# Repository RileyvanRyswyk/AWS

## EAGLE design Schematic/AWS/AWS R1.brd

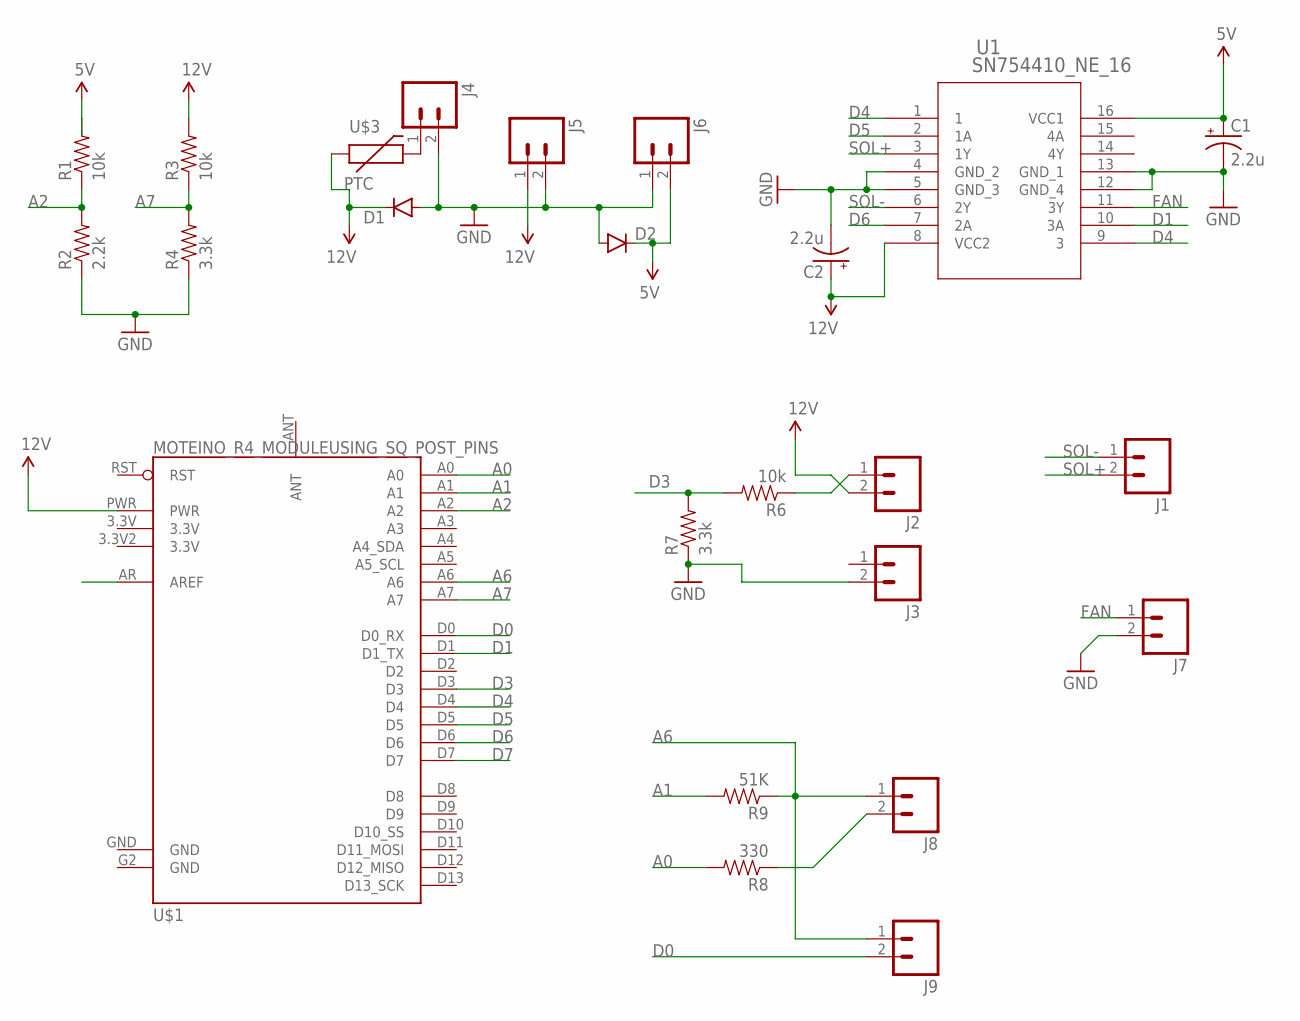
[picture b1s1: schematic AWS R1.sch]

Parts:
C1, C2: 2.2u; CPOL-RADIAL-100UF-25V
D1, D2: DIODEPTH; DIODE-1N4001
J1, J2, J3, J4, J5, J6, J7, J8, J9: M025MM; SCREWTERMINAL-5MM-2
R1, R3, R6: 10k; AXIAL-0.4
R2: 2.2k; AXIAL-0.4
R4, R7: 3.3k; AXIAL-0.4
R8: 330; AXIAL-0.4
R9: 51K; AXIAL-0.4
U1: SN754410_NE_16; NE16
U$1: MOTEINO_R4_MODULEUSING_SQ_POST_PINS; MOTEINTO_R4_SQ
U$3: PTC; MC331XX

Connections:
5V: C1.1 (+), D2.C, J6.2, R1.P$2 (2), U1.16 (VCC1)
12V: C2.1 (+), D1.C, J2.2, J5.1, R3.P$2 (2), U1.8 (VCC2), U$1.PWR, U$3.P$1 (1)
A0: R8.P$2 (2), U$1.A0
A1: R9.P$2 (2), U$1.A1
A2: R1.P$1 (1), R2.P$2 (2), U$1.A2
A6: J8.1, J9.1, R9.P$1 (1), U$1.A6
A7: R3.P$1 (1), R4.P$2 (2), U$1.A7
D0: J9.2, U$1.D0 (D0_RX)
D1: U1.10 (3A), U$1.D1 (D1_TX)
D3: R6.P$2 (2), R7.P$2 (2), U$1.D3
D4: U1.1, U1.9 (3), U$1.D4
D5: U1.2 (1A), U$1.D5
D6: U1.7 (2A), U$1.D6
D7: U$1.D7
FAN: J7.1, U1.11 (3Y)
GND: C1.2 (-), C2.2 (-), D1.A, D2.A, J3.2, J4.2, J5.2, J6.1, J7.2, R2.P$1 (1), R4.P$1 (1), R7.P$1 (1), U1.4 (GND_2), U1.5 (GND_3), U1.12 (GND_4), U1.13 (GND_1), U$1.G2 (GND), U$1.GND
unnamed: J8.2, R8.P$1 (1)
unnamed: J2.1, R6.P$1 (1)
unnamed: J4.1, U$3.P$2 (2)
SOL+: J1.2, U1.3 (1Y)
SOL-: J1.1, U1.6 (2Y)

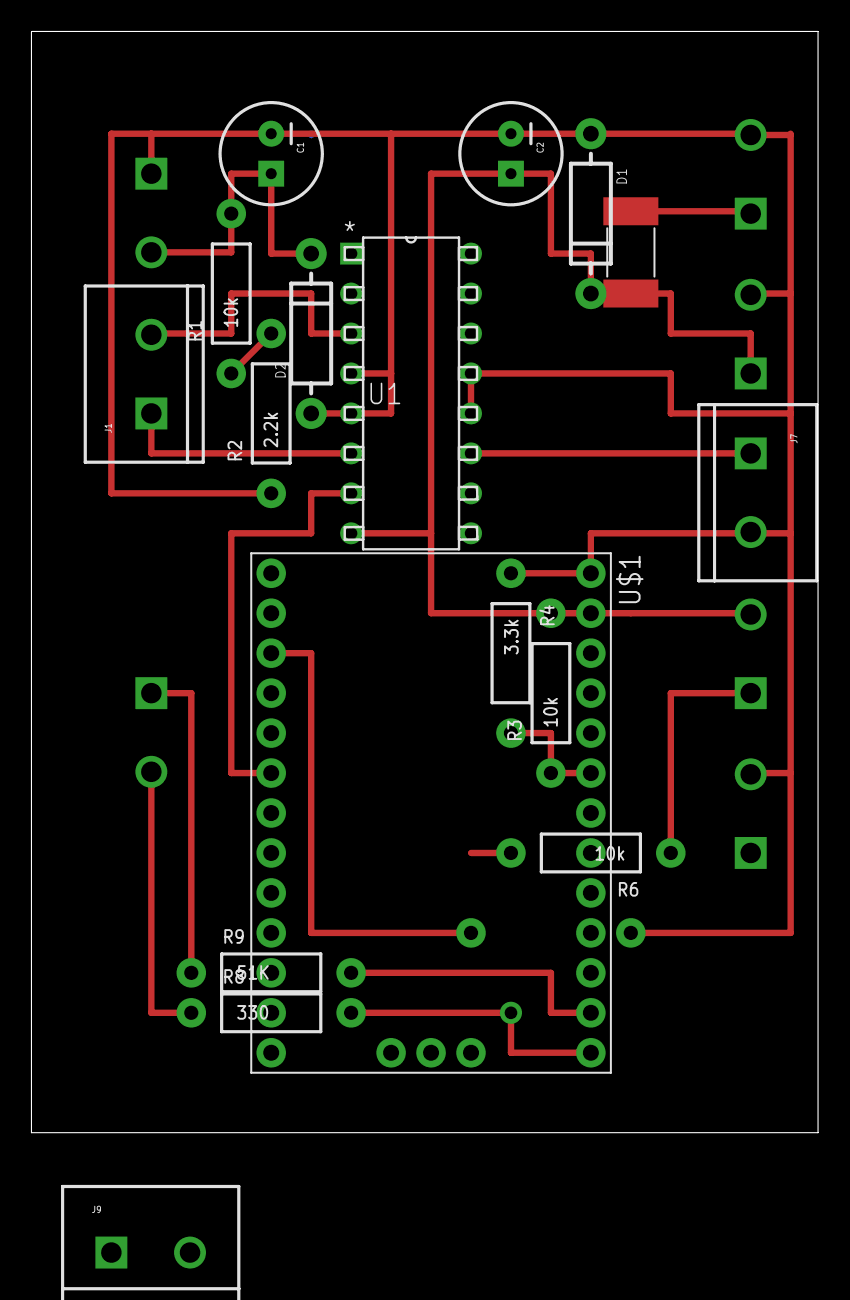
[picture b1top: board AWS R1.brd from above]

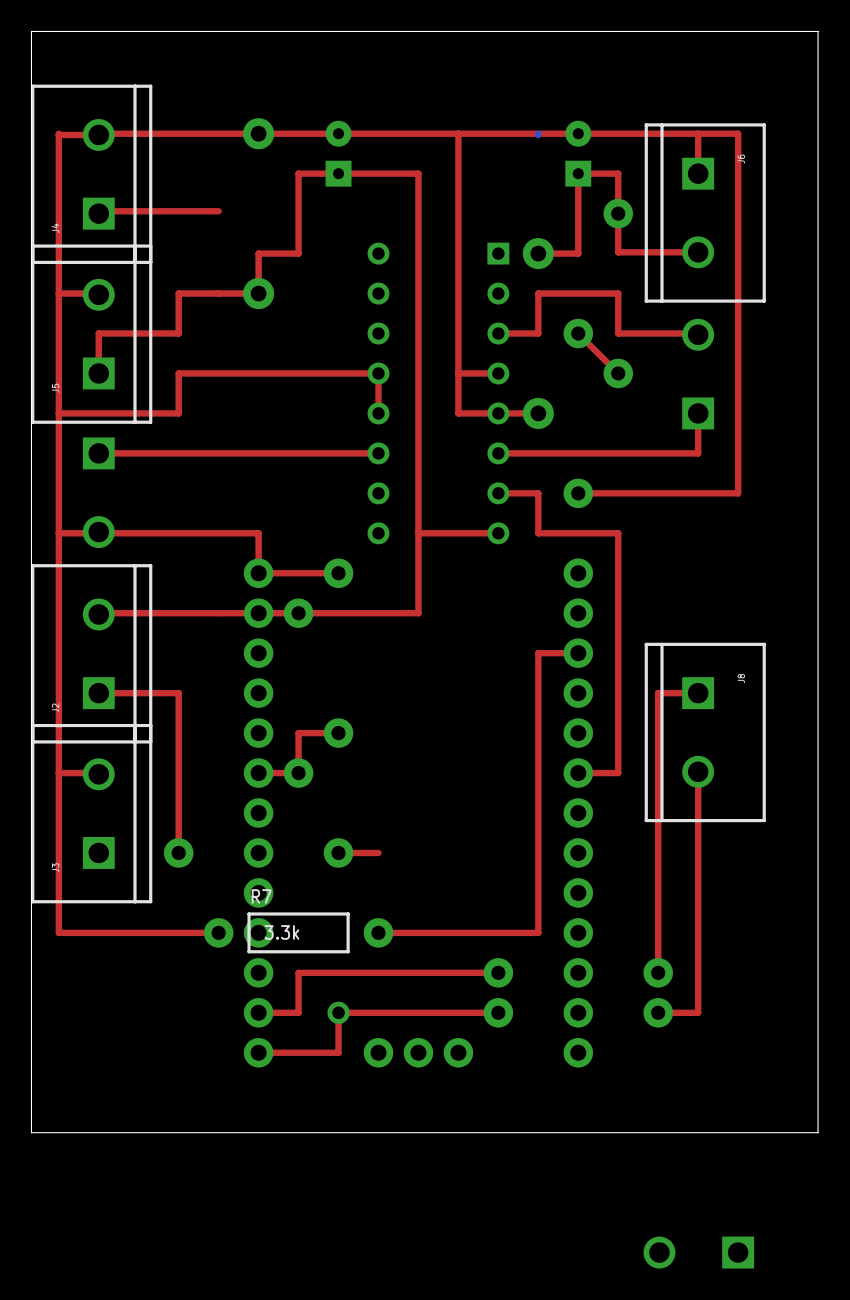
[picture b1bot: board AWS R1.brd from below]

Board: 2 copper layers, 50.0 x 70.0 mm, 24 parts (7 on the bottom side), 20 nets.

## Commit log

2016-06-14 :tada: Added .gitattributes & .gitignore files
2016-06-14 Initial
2016-06-15 Removed Orcad Files
2016-06-15 R0 Eagle Schematic
2016-06-15 Old Code
2016-06-15 Updated Resistor value
    And remove .s#* files
2016-06-15 updated gitignore
2016-06-15 autosave removed
2016-06-15 Visual Studio gitignore
2016-06-15 Wireless Programming Works!
2016-06-15 Read Voltage Function works
2016-06-16 Fan Working
2016-06-16 Valve Works!
2016-06-17 All Basic Functions Working!
2016-06-17 Completed the board layout
2016-06-19 Board files
2016-06-20 Modified Board
2016-06-20 final
2016-06-22 Moved outside
2016-06-22 Removed 10k pullup on flow sensor
2016-06-22 Add filtering for soil measurement
2016-06-24 Commands Work!
2016-06-24 Cleaning up libaries
2016-06-24 Added WDT
    And renaming
2016-06-24 Project Files.
2016-06-30 Added basic python scheduling
2016-07-07 Added get sensor data
2016-07-10 update db_schema to v1
2016-07-10 auto multi-message created
2016-07-10 Adds sensordata to the database
2016-07-10 Soil Measurement Data
2016-07-10 redid getSensorData to extract soil measurement
2016-07-11 Updated to 10 min averaging window
2016-07-11 Changed to get data every 5 mins
2016-07-11 Added design stuff
2016-07-11 Updated sensor reading intervals
2016-07-12 Committing to be able to revert
2016-07-13 Finally solved the soil moisture issues...i think
2016-07-13 Fixed bug with calculating Q
2016-07-13 Added a way to manually water
2016-07-13 Started a design
2016-07-25 Sail.js default files
2016-07-25 Updated design files (schedule design mostly complete)
2016-07-27 Reorganized web files in BaseStation
2016-07-27 Update pass
2016-07-27 old config

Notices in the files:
parts and their libraries:
SparkFun-Capacitors: Licensing: Creative Commons ShareAlike 4.0 International - https://creativecommons.org/licenses/by-sa/4.0
